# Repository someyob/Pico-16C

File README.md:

Hi there, while you're here, maybe check out the newer version of this project:
https://github.com/someyob/Pico16cV2

# Pico-16C

Notes for new version 0.5:
  - added floating point entry and operations.  Note that CicruitPython only uses single precision floats, so some results will seem unexpected.  < examples follow >  I may restrict the number of decimal places (for example, entering float mode by pressing f-FLOAT-{0..9,.}, where 0 to 9 represents the number of decimal points you want to work with) to 5, even though that doesn't really mitigate the issue.  Best option would be for CircuitPython to match what Python 3 is able to handle double precision floats.  Not going to get hung up on it, as I would typically not frequently use the calculator for floating point calculations.
  - Differences between Pico16C 0.5 and the HP 16C:
      - switching from an integer base to floating point will convert what's in the X register, but the opposite is not true.  Further, the conversion from integer to float simply changes the representation, not the number.  The stack is unchanged, and the word size is ignored.
      - added a 'hidden function' to allow for a 'thousands separator' (eg. 64,636) to make readability better for long numbers.  Unfortunately, separators do not work for binary and hex representations (eg. 1100 1100 0001, or FFEH AE12) due to a bug in CicruitPython as of version 8)

Wanted an HP 16C calculator, the gold standard for early programmers.  Didn't have one, too cheap to buy one off eBay, and while the new ones you can get from SwissMicro https://www.swissmicros.com/product/dm16l look great, they don't scratch my other itch, which is to play with microcontrollers and learn a new language (python).

Python is well suited to this application given a full suite of excellent string manipulation and math libraries, adafruit libraries, etc.  Execution speed is not an issue.

I was helped a lot during development with access to a couple of different software emulators out there (http://www.hp16c.org/ and https://stendec.io/ctb/rpn_prog.html), especially when I can see what's happening with the stack.  The manual https://literature.hpcalc.org/community/hp16c-oh-en.pdf was also essential reading.

An early version of this project got a mention on the Raspberry Pi blog https://www.raspberrypi.com/news/replica-hp-16c-coding-calculator/ and on Adafruit's Python on Hardware newsletter https://blog.adafruit.com/2022/10/19/icymi-python-on-microcontrollers-newsletter-ladyada-at-espressif-devcon-this-week-circuitpython-8-beta-2-and-more-circuitpython-icymi-raspberrypi-micropython-raspberry_pi/

Tools and materials used:
  - Raspberry Pi Pico
  - 1602 LCD display (w. i2c backpack)
  - breadboards and soldering iron
  - perfboard, w. 22awg wire
  - level shifter module (only using 2 out of 4 lines for i2c)
  - two 3x4 and one 4x4 aliexpress keypads (modified to jam as close together as possible)
  - 3d Printer
  - Glue gun
  - PTouch Labelmaker
  - Laser printer (for keypad overlay), highlighter pens
  - Thonny with Circuitpython 7.2.3
  
The software emulates (mimics) the basic operations of a 16C, all in Reverse Polish Notation (RPN) with the standard X, Y, Z and T registers.
What it's currently capable of:
  - integer entry in either hexadecimal, octal, decimal or binary
  - conversions between those bases
  - ordinary arithmatic (+ - / *), some bitwise operations (NOT, AND, etc)
  - stack operations x<->y, R^, Rv, LastX
  
Differences between this and a real 16C:
  - maximum 128 bit words (vs 16C 64 bit)
  - 16 character display, with eight 16 character windows, scrolling with shift-g < and > keys
  - 'Enter' key is standard size, not double lenth like a real 16C
  - Has a splash screen that gives you the current version number
  - Has a timeout feature that turns off the LCD after 5 minutes (hard coded)
  - The calculator is always 'running', ON and OFF simply turns off the display and backlight

Work to come in the near future:
  - floating point
  - more bitwise operations, 1's and 2's complement arithmetic

Work to come in the far future (if ever):
  - Programming mode

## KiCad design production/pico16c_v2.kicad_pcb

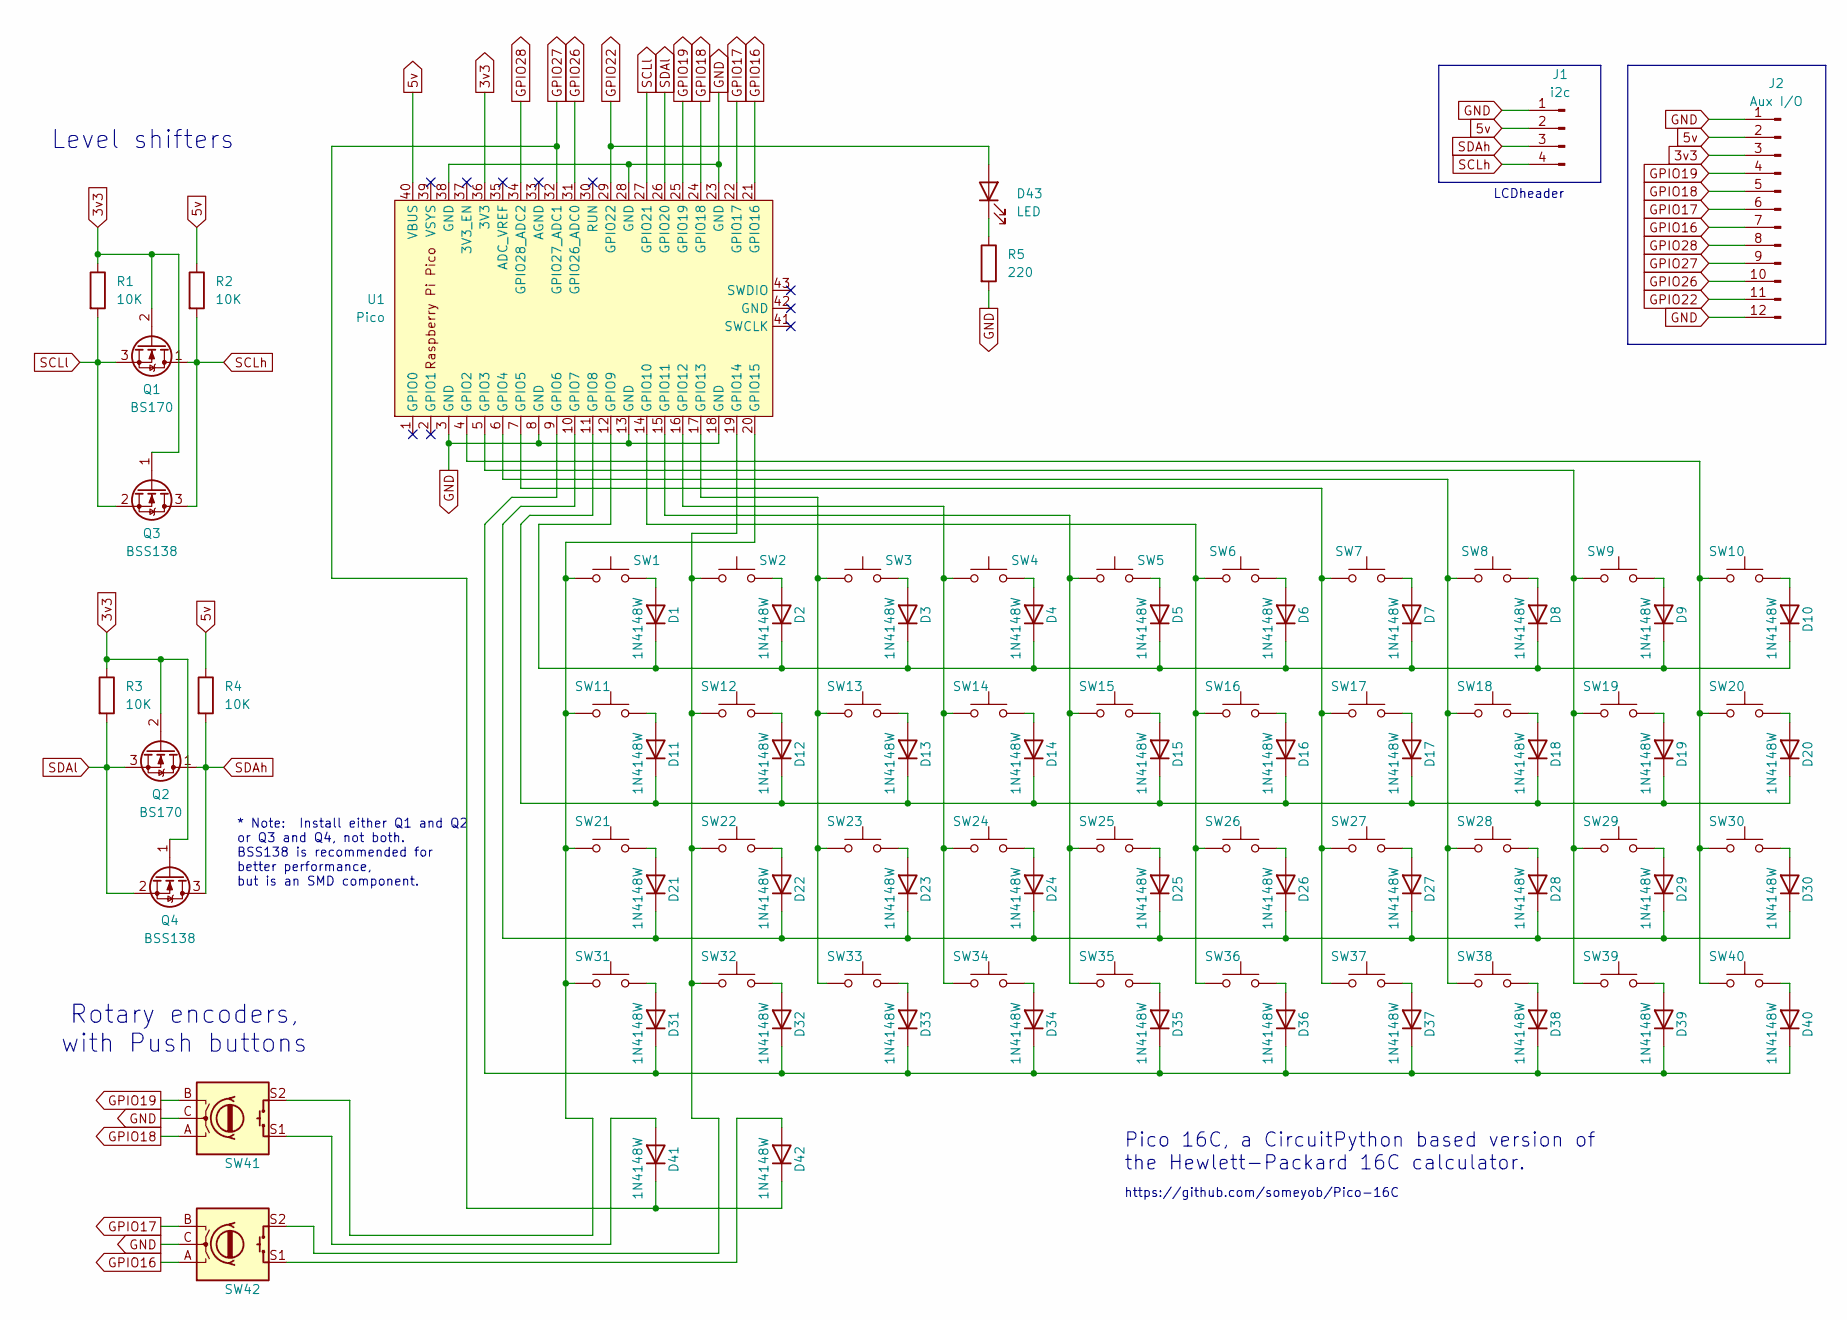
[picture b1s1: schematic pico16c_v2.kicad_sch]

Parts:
D1, D2, D3, D4, D5, D6, D7, D8, D9, D10, D11, D12, D13, D14, D15, D16, D17, D18, D19, D20, D21, D22, D23, D24, D25, D26, D27, D28, D29, D30, D31, D32, D33, D34, D35, D36, D37, D38, D39, D40, D41, D42: 1N4148W; D_DO-35_SOD27_P7.62mm_Horizontal
D43: LED; LED_D2.0mm_W4.0mm_H2.8mm_FlatTop
J1: i2c; PinHeader_1x04_P2.54mm_Vertical
J2: Aux I/O; PinHeader_1x12_P2.54mm_Vertical
Q1, Q2: BS170; TO-92_Inline
Q3, Q4: BSS138; SOT-23
R1, R2, R3, R4: 10K; R_Axial_DIN0207_L6.3mm_D2.5mm_P10.16mm_Horizontal
R5: 220; R_Axial_DIN0207_L6.3mm_D2.5mm_P10.16mm_Horizontal
SW1, SW2, SW3, SW4, SW5, SW6, SW7, SW8, SW9, SW10, SW11, SW12, SW13, SW14, SW15, SW16, SW17, SW18, SW19, SW20, SW21, SW22, SW23, SW24, SW25, SW26, SW27, SW28, SW29, SW30, SW31, SW32, SW33, SW34, SW35, SW36, SW37, SW38, SW39, SW40: SW_Push; SW_Cherry_MX_1.00u_PCB
SW41, SW42: Encoder_Switch; RotaryEncoder_Alps_EC11E-Switch_Vertical_H20mm
U1: Pico; RPi_Pico_SMD_TH

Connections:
3v3: J2.3, Q1.2 (G), Q2.2 (G), Q3.1 (G), Q4.1 (G), R1.1, R3.1, U1.36 (3V3)
5v: J1.2, J2.2, R2.1, R4.1, U1.40 (VBUS)
GND: J1.1, J2.1, J2.12, R5.2, SW41.C, SW42.C, U1.3 (GND), U1.8 (GND), U1.13 (GND), U1.18 (GND), U1.23 (GND), U1.28 (GND), U1.38 (GND)
GPIO16: J2.7, SW42.A, U1.21 (GPIO16)
GPIO17: J2.6, SW42.B, U1.22 (GPIO17)
GPIO18: J2.5, SW41.A, U1.24 (GPIO18)
GPIO19: J2.4, SW41.B, U1.25 (GPIO19)
GPIO22: D43.2 (A), J2.11, U1.29 (GPIO22)
GPIO26: J2.10, U1.31 (GPIO26_ADC0)
GPIO27: D41.1 (K), D42.1 (K), J2.9, U1.32 (GPIO27_ADC1)
GPIO28: J2.8, U1.34 (GPIO28_ADC2)
unnamed: D1.2 (A), SW1.1
unnamed: D1.1 (K), D2.1 (K), D3.1 (K), D4.1 (K), D5.1 (K), D6.1 (K), D7.1 (K), D8.1 (K), D9.1 (K), D10.1 (K), U1.12 (GPIO9)
unnamed: D2.2 (A), SW2.1
unnamed: D3.2 (A), SW3.1
unnamed: D4.2 (A), SW4.1
unnamed: D5.2 (A), SW5.1
unnamed: D6.2 (A), SW6.1
unnamed: D7.2 (A), SW7.1
unnamed: D8.2 (A), SW8.1
unnamed: D9.2 (A), SW9.1
unnamed: D10.2 (A), SW10.1
unnamed: D11.2 (A), SW11.1
unnamed: D11.1 (K), D12.1 (K), D13.1 (K), D14.1 (K), D15.1 (K), D16.1 (K), D17.1 (K), D18.1 (K), D19.1 (K), D20.1 (K), U1.11 (GPIO8)
unnamed: D12.2 (A), SW12.1
unnamed: D13.2 (A), SW13.1
unnamed: D14.2 (A), SW14.1
unnamed: D15.2 (A), SW15.1
unnamed: D16.2 (A), SW16.1
unnamed: D17.2 (A), SW17.1
unnamed: D18.2 (A), SW18.1
unnamed: D19.2 (A), SW19.1
unnamed: D20.2 (A), SW20.1
unnamed: D21.2 (A), SW21.1
unnamed: D21.1 (K), D22.1 (K), D23.1 (K), D24.1 (K), D25.1 (K), D26.1 (K), D27.1 (K), D28.1 (K), D29.1 (K), D30.1 (K), U1.10 (GPIO7)
unnamed: D22.2 (A), SW22.1
unnamed: D23.2 (A), SW23.1
unnamed: D24.2 (A), SW24.1
unnamed: D25.2 (A), SW25.1
unnamed: D26.2 (A), SW26.1
unnamed: D27.2 (A), SW27.1
unnamed: D28.2 (A), SW28.1
unnamed: D29.2 (A), SW29.1
unnamed: D30.2 (A), SW30.1
unnamed: D31.2 (A), SW31.1
unnamed: D31.1 (K), D32.1 (K), D33.1 (K), D34.1 (K), D35.1 (K), D36.1 (K), D37.1 (K), D38.1 (K), D39.1 (K), D40.1 (K), U1.9 (GPIO6)
unnamed: D32.2 (A), SW32.1
unnamed: D33.2 (A), SW33.1
unnamed: D34.2 (A), SW34.1
unnamed: D35.2 (A), SW35.1
unnamed: D36.2 (A), SW36.1
unnamed: D37.2 (A), SW37.1
unnamed: D38.2 (A), SW38.1
unnamed: D39.2 (A), SW39.1
unnamed: D40.2 (A), SW40.1
unnamed: D41.2 (A), SW41.S1
unnamed: D42.2 (A), SW42.S1
unnamed: D43.1 (K), R5.1
unnamed: SW10.2, SW20.2, SW30.2, SW40.2, U1.4 (GPIO2)
unnamed: SW9.2, SW19.2, SW29.2, SW39.2, U1.5 (GPIO3)
unnamed: SW8.2, SW18.2, SW28.2, SW38.2, U1.6 (GPIO4)
unnamed: SW7.2, SW17.2, SW27.2, SW37.2, U1.7 (GPIO5)
unnamed: SW6.2, SW16.2, SW26.2, SW36.2, U1.14 (GPIO10)
unnamed: SW5.2, SW15.2, SW25.2, SW35.2, U1.15 (GPIO11)
unnamed: SW4.2, SW14.2, SW24.2, SW34.2, U1.16 (GPIO12)
unnamed: SW3.2, SW13.2, SW23.2, SW33.2, U1.17 (GPIO13)
unnamed: SW2.2, SW12.2, SW22.2, SW32.2, SW42.S2, U1.19 (GPIO14)
unnamed: SW1.2, SW11.2, SW21.2, SW31.2, SW41.S2, U1.20 (GPIO15)
SCLh: J1.4, Q1.1 (D), Q3.3 (D), R2.2
SCLl: Q1.3 (S), Q3.2 (S), R1.2, U1.27 (GPIO21)
SDAh: J1.3, Q2.1 (D), Q4.3 (D), R4.2
SDAl: Q2.3 (S), Q4.2 (S), R3.2, U1.26 (GPIO20)

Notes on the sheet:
Pico 16C, a CircuitPython based version of the Hewlett-Packard 16C calculator.
https://github.com/someyob/Pico-16C
LCDheader
* Note: Install either Q1 and Q2 or Q3 and Q4, not both. BSS138 is recommended for better performance, but is an SMD component.
Rotary encoders, with Push buttons
Level shifters

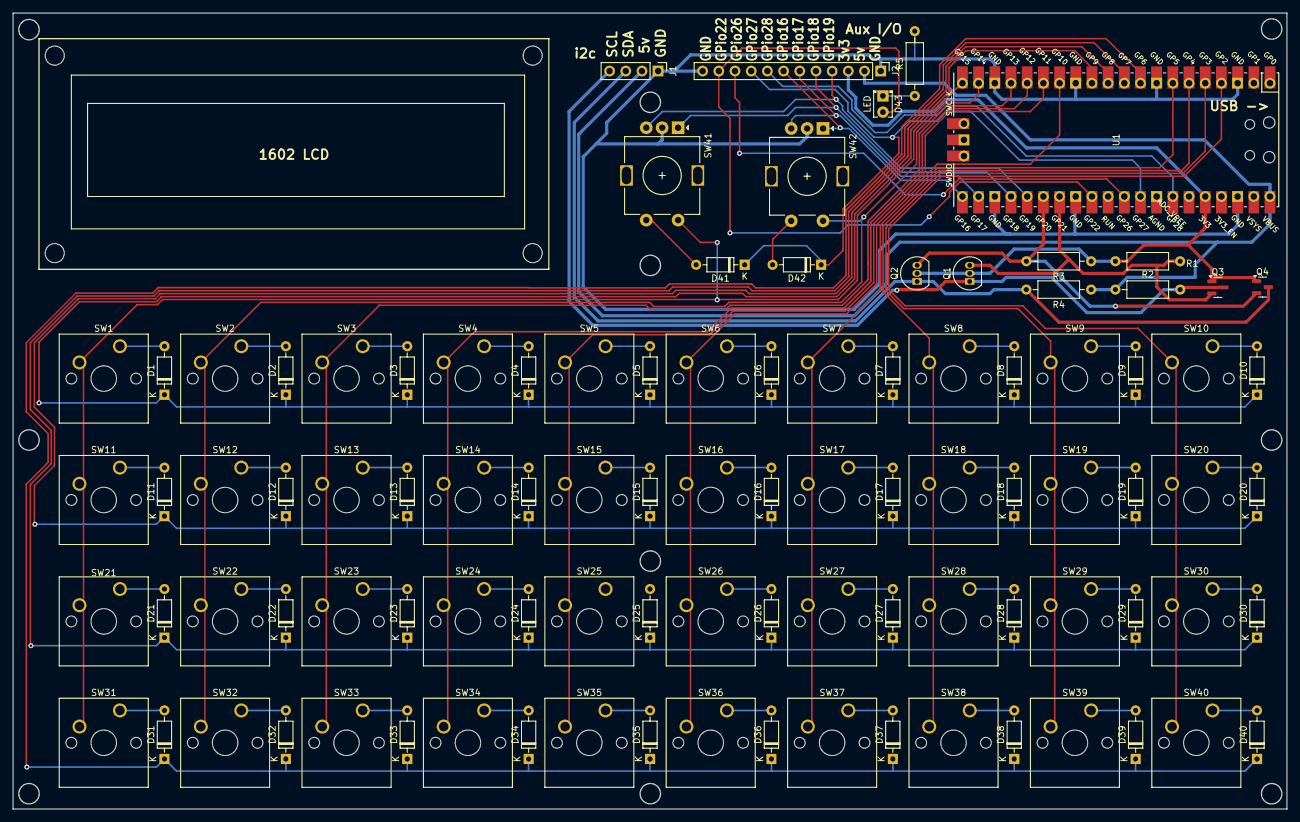
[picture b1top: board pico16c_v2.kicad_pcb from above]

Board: 2 copper layers, 199.8 x 124.8 mm, 97 parts (0 on the bottom side), 72 nets.

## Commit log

2022-12-09 Old versions
    Upload early version
2022-12-09 v0.3
    Continued development
2022-12-13 new ver duh
